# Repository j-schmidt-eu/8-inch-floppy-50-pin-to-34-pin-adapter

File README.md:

# 8-inch floppy drive - 50-pin to 34-pin adapter Rev. 2

> The 50-pin to 34-pin adapter can be used to adapt 8-inch floppy disk drives (using a 50-pin connector) to be controlled by 3.5-inch and 5.25-inch floppy controllers (using a 34-pin connector).

## Table of Contents
- [Introduction](#Introduction)
- [Specifications](#Specifications)
- [Setup](#Setup)
- [Operation](#Operation)
- [Compatibility](#Compatibility)
- [Manufacturing](#Manufacturing)
- [Firmware](#Firmware)
- [FAQ](#FAQ)
- [Licensing](#Licensing)

## Introduction
Many 8-inch floppy drives use a 50-pin card-edge connector to link them to a controller. This is a problem, since modern floppy controllers use a 34-pin IDC connector.
To solve this problem an adapter is necessary that connects compatible signals and generates signals that are unique to the 8-inch floppy drives.
This project aims to provide the schematic, PCB design and firmware source code to build such an adapter.
All compatible signals are directly linked from the 50-pin connector to the 34-pin connector.
Other signals are generated with an onboard microcontroller.

## Specifications
- Power
  - Input voltage: 5V DC
  - Maximum input current: 750mA
  - Connector: 4-pin Berg/Amphenol
- Maximum number of drives per adapter: 2
- Maximum number of adapters per controller: 1
- Pass-through signals:

  | Direction | Name |
  | --------- | ---- |
  | IN        | Index |
  | OUT       | Drive select A |
  | OUT       | Drive select B |
  | OUT       | Direction |
  | OUT       | Step |
  | OUT       | Write data |
  | OUT       | Write gate |
  | IN        | Track 0 |
  | IN        | Write protect |
  | IN        | Read data |
  | OUT       | Side select |
- Generated signals:

  | Direction | Name | Signal source |
  | --------- | ---- | ------------- |
  | OUT       | TG43 (Track greater than 43) /<br>Reduce write current /<br>Filter switch | Determined by tracking the head position.<br>Multiple options available (e.g. control via external signal) |
  | OUT       | Head load | Derived from Motor enable signal.<br>Multiple options available (e.g. control via external signal) |
  | IN        | Ready | Derived from ready signal.<br>Can be disabled by removing a solder jumper bridge JP1 |

## Setup
The adapter can drive up to two drives.

### Floppy drive
A single drive should always be jumpered to be drive A.
The drive should have the termination resistors enabled/present.

A two drive setup should have one drive jumpered to be drive A and the other to be drive to be jumpered drive B.
The last drive (the drive connected at the end of the 50-pin ribbon cable) should have the termination resistors enabled/present, the other drive must have the termination resistors disabled/removed.

__**Important: Only one set of termination resistors must be enabled/present! Having more than one termination resistors enabled/present can damage the adapter and the floppy controller!**__

### Connections

#### Data
To connect the controller to the adapter, use a 34-pin ribbon cable (IDC socket connector to IDC socket connector).
It is recommended to connect the adapter after the twist in the ribbon cable. 

_Note: **When using straight cable without twist, drive A and drive B will be swapped on the controller side.**_

The drive(s) should be connected to the adapter with a 50-pin ribbon cable (IDC card edge connector to IDC socket connector).

#### Power
The adapter should be connected to a power supply via the 4 pin Berg/Amphenol connector (only the 5V line will be used). The pinout is ATX compatible.
Power for the floppy drive(s) should be supplied as described in the operations manual for that specific drive.

## Operation
To operate the adapter a single push button (command button) is present on the bottom right corner of the PCB.

_Note: **The button will be disabled when any drive is in use.**_

### Display
For status display and settings, a two-digit seven-segment display is present on the top right corner of the PCB.
A short press on the command button can be used to cycled between the following display modes:

| Mode | Dot status | Description | Range |
| ---- | ---- | ----------- | ----- |
| Track | Left: off<br>Right: on | Current head position | 0 ... 80 |
| Speed | Left: on (positive value) / blink (negative value)<br>Right: off | Percent deviation from nominal rotational speed | -9.9% ... 9.9% |
| Revision | Left: blink<br>Right: blink<br>Alternates between left and right | Software revision number | 1 ... 99 |
| Dark | Left: off<br>Right: off | Disables display | - |

### Settings
To edit the settings of the adapter the setup menu can be entered by pressing the command button for longer than two seconds.
When navigating the setup menu both dots will be lit.
A short press on the command button can be used to cycled between the menu items.
Item value editing can be enabled and disabled by pressing the command button for longer than two seconds.
During editing both dots will blink simultaneously.
A short press on the command button can be used to cycled between value.

To exit the setup menu, navigate to the Exit item and press the command button for longer than two seconds.

The following menu items are available (in listed order):

| Item | Display | Description | Values | Default |
| ---- | ------- | ----------- | ------ | ------- |
| Default display mode | Left: 1<br>Right: value | Default display mode after adapter power up | 0: Track<br>1: Speed<br>2: Revision<br>3: Dark | 0: Track |
| Drive A<br>Maximum track number | Left/Right: value | Maximum track number that the drive can step to | 32 ... 80 | 76 |
| Drive A<br>TGxx signal | Left: 3<br>Right: value | Source for TG43 / reduce write current / filter signal | 0: Use thresholds<br>1: Always active<br>2: Always inactive<br>3: From external signal | 0: Use thresholds |
| Drive A<br>Head load signal | Left: 4<br>Right: value | Source for head load signal | 0: From [motor A enable]<br>1: Always active<br>2: Always inactive<br>3: From external signal | 0: From [motor A enable] |
| Drive A<br>TGxx write threshold | Left/Right: value | Track number threshold (greater or equal) for TGxx signal active when writing | 0 ... 99 | 44 |
| Drive A<br>TGxx read threshold | Left/Right: value | Track number threshold (greater or equal) for TGxx signal active when reading | 0 ... 99 | 99 |
| Drive B<br>Maximum track number | Left/Right: value | Maximum track number that the drive can step to | 32 ... 80 | 76 |
| Drive B<br>TGxx signal | Left: 8<br>Right: value | Source for TG43 / reduce write current / filter signal | 0: Use thresholds<br>1: Always active<br>2: Always inactive<br>3: From external signal | 0: Use thresholds |
| Drive B<br>Head load signal | Left: 9<br>Right: value | Source for head load signal | 0: From [motor B enable]<br>1: Always active<br>2: Always inactive<br>3: From external signal | 0: From [motor B enable] |
| Drive B<br>TGxx write threshold | Left/Right: value | Track number threshold (greater or equal) for TGxx signal active when writing | 0 ... 99 | 44 |
| Drive B<br>TGxx read threshold | Left/Right: value | Track number threshold (greater or equal) for TGxx signal active when reading | 0 ... 99 | 99 |
| Exit | Left/Right: dark | - | - | - |

_Note: **The external signal cannot distinguish between multiple signals, therefore it should only be assigned to a single signal.**_

The settings are permanently stored when exiting the setup menu.

## Compatibility
The following list shows some 8-inch floppy drive models and the respective settings that should be correct for them.

| Model | TGxx signal | TGxx write threshold | TGxx read threshold | Head load signal | Maximum track number<sup>1</sup> | Tested<sup>2</sup> |
| ----- | ----------- | -------------------- | ------------------- | ---------------- | -------------------- | ------ |
| Mitsubishi M2896-63 | 0: Use thresholds <sup>4</sup> | 44 | 99 | 0: From [motor enable]  | 76(?) | ❓ |
| NEC FD1165 | 0: Use thresholds | 44 | 44 | 0: From [motor enable] | 76(?) | ❓ |
| Shugart SA800<br>Shugart SA801 | 0: Use thresholds <sup>3</sup> | 44 | 99 | 0: From [motor enable] <sup>4</sup> | 76(?) | ❓ |
| Shugart SA810<br>Shugart SA860 | 0: Use thresholds <sup>4</sup> | 44 | 99 | 0: From [motor enable] <sup>4</sup> | 76(?) | ❓ |
| Shugart SA850<br>Shugart SA851 | 0: Use thresholds <sup>4</sup> | 44 | 99 | 0: From [motor enable] <sup>4</sup> | 76(?) | ❓ |
| Tandon TM848-1E<br>Tandon TM848-2E | 0: Use thresholds <sup>4</sup> | 44 | 99 | 0: From [motor enable] <sup>4</sup> | 76(?) | ❓ |
| Y-E DATA YD-180 | 0: Use thresholds | 44 | 60 | 0: From [motor enable] <sup>4</sup> | 79 | ✅ |

<sup>1</sup> Actual seekable track number; track numbering starts at zero.<br>
<sup>2</sup> ✅: Settings have been successfully tested. ❓: Settings should be correct according to the manual, but haven't been tested yet.<br>
<sup>3</sup> Switching is done internally.<br>
<sup>4</sup> Switching is done internally by default; external switching is available optionally (see manual).

## Manufacturing
The schematics and PCB were designed using [KiCad](https://kicad-pcb.org/). The KiCad project is located in the [Schematics & PCB](Schematics%20&%20PCB) folder. 

### Schematic
[PDF](Schematics%20&%20PCB/50%20pin%20to%2034%20pin%20Floppy%20Adapter%20v2/50%20pin%20to%2034%20pin%20Floppy%20Adapter.pdf)

[PNG](Schematics%20&%20PCB/50%20pin%20to%2034%20pin%20Floppy%20Adapter%20v2/50%20pin%20to%2034%20pin%20Floppy%20Adapter.png)

### PCB Gerber files
[ZIP](Schematics%20&%20PCB/50%20pin%20to%2034%20pin%20Floppy%20Adapter%20v2/pcb.zip)

### PCB manufacturing
The board has a size of 100mm x 28.5mm, a minimum trace distance of 0.2mm and the minimal drill diameter is 0.4mm.
There are two layers and a total of 166 holes to drill. All holes, except for the two mounting holes, are plated.

If you are within the EU, you may want to consider choosing AISLER as your PCB manufacturer.

[PCB on AISLER](https://aisler.net/p/LBENFXQV)

### Bill of materials
| Reference | Component | Housing /<br>Footprint | Type | Quantity |
| --------- | --------- | ---------------------- | ---- | -------- |
| C1 | Capacitor 100nF 10V | 0402 | Murata GRM155R61A104JA01D<sup>5</sup> | 1 |
| C2 | Tantalum Capacitor 10µF 6.3V  | B / EIA-3528-21 | Kemet T491B106K006AT<sup>5</sup>  | 1 |
| J1 | 34 pin box header | 2 x 17 x 2.54mm | Connfly DS1013-34SSIB1-B-0<sup>5</sup> | 1 |
| J2 | 4 pin Berg connector | 1 x 4 x 2.54mm | econ connect FK03PN<sup>5</sup> | 1 |
| J3 | 50 pin box header | 2 x 25 x 2.54mm | Connfly DS1013-50SSIB1-B-0<sup>5</sup> | 1 |
| ~~J4~~<sup>6</sup> | ~~3 pin header~~ | ~~1 x 3 x 2.54mm~~ | ~~Connfly DS1021-1*3SF1-1~~<sup>5</sup> | ~~1~~ |
| J5 | 5 pin socket | 1 x 5 x 2.54mm | Connfly DS1023-1*5S21<sup>5</sup> | 1 |
| R2 | Resistor 22kOhm 1/8W 5% | 0805 | Vishay CRCW080522K0FKEA<sup>5</sup> | 1 |
| R1, R3-R4 | Resistor 1kOhm 1/8W 5% | 0805 | Vishay CRCW08051K00FKEA<sup>5</sup> | 3 |
| RN1-RN2, RN5-RN6 | Resistor array 150Ohm 1/16W 5% | 4 x 0603 (1206) convex | Panasonic EXB38V151JV<sup>5</sup> | 4 |
| SW1 | SMD Push button 6mm x 6mm | 9.5mm x 5.8mm | C&K PTS645SK50SMTR92LFS<sup>5</sup> | 1 |
| U1 | PIC18 MCU | QFN-28, 6mm x 6mm, pitch 0.65mm | Microchip PIC18F26K22-I/ML | 1 |
| U2-U3 | BCD to 7-segment decoder | SOP-16, 4.55mm x 10.3mm, pitch 1.27mm | NXP HEF4543B | 2 |
| U4 | Dual buffer | SOT-363 / SC-70-6 | ON Semi NC7WZ16P6X | 1 |
| U5-U6 | Seven segment display | 7mm x 15mm | Kingbright KCSA03-101 | 2 |
| U8 | Dual three-state buffer | VSSOP-8, 2.3mm x 2mm, pitch 0.5mm | ON Semi NC7WZ125K8X | 1 |

<sup>5</sup> Suggestion; Other types may be used. <br>
<sup>6</sup> Not populated; Pin header may be placed, when needed.

### PCB component placement
When soldering the components to the PCB, it is recommended to place them in the following order:
1. Bottom side, hot air: RN1-RN2, RN5-RN6, R2, U2, U3, U8
2. Top side, hot air: C1, C2, R1, R3, R4, U4, U1
3. Top side, soldering iron: U5, U6, SW1, J1, J3, J5, J2
4. Do not populate: J4 (place pin header when needed)

## Firmware
The software for the microcontroller was designed in [MPLAB X IDE](https://www.microchip.com/mplab/mplab-x-ide).
It is written in C and compiled with the [MPLAB XC8 compiler](https://www.microchip.com/mplab/compilers).
A programming adapter is required to transfer the firmware into the microcontroller. The programming socket J5 is designed to match the pinout of the [MPLAB PICkit 4](https://www.microchip.com/developmenttools/ProductDetails/PG164140) (and older) programmers.
The MPLAB X IDE project is located in the [Firmware](Firmware) folder. 

## FAQ
##### My drive is not listed in the compatibility list, will it work?
>**Check the manual of your drive to see if it needs any additional signals like TG43 and Head load.
If so, check if one of the available options matches the behavior required by the drive. When that is the case, the drive will very likely work.**

## Licensing
This project is licensed under the [CC BY-NC-ND 4.0 license](LICENSE).

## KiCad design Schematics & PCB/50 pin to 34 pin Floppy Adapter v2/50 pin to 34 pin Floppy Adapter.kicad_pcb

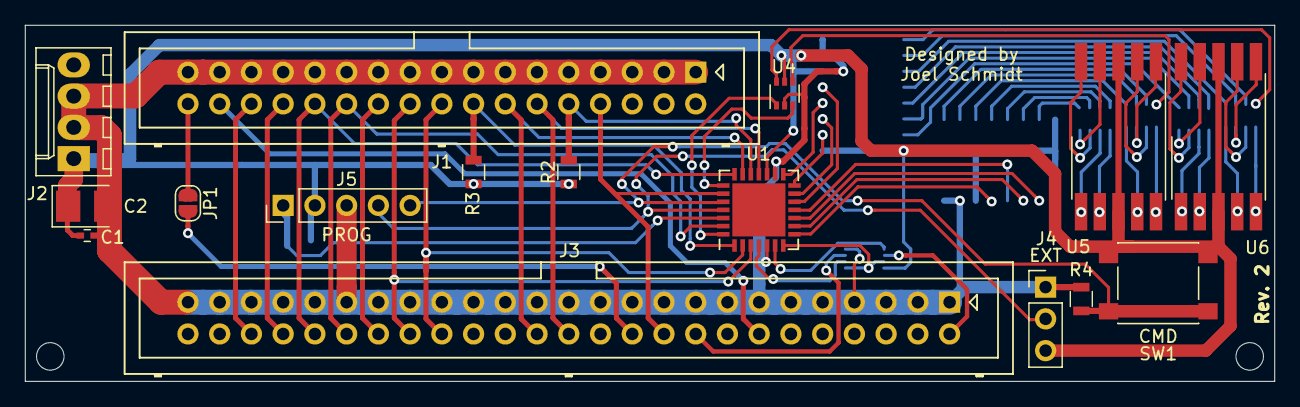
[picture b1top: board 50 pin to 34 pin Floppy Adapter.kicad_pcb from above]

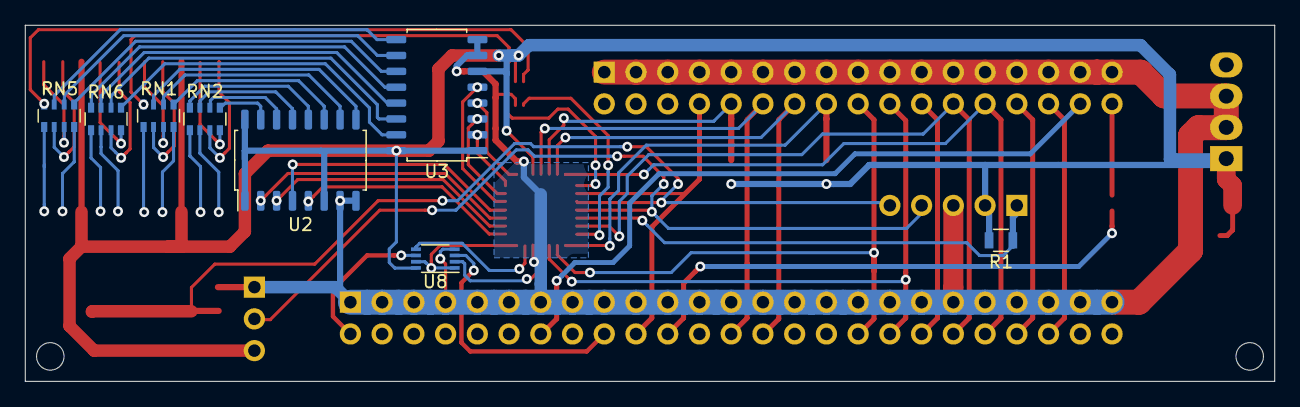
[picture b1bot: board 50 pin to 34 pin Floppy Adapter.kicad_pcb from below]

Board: 2 copper layers, 100.0 x 28.5 mm, 24 parts (8 on the bottom side), 67 nets.

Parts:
C1: 100n; C_0402
C2: 10u; CP_Tantalum_Case-B_EIA-3528-21_Reflow
J1: PC34; Multicomp_MC9A12-3434_2x17x2.54mm_Straight
J2: PWR; TE_171825-4x2.50mm_Straight
J3: FDD50; Multicomp_MC9A12-5034_2x25x2.54mm_Straight
J4: EXT; Pin_Header_Straight_1x03_Pitch2.54mm
J5: PROG; Pin_Header_Straight_1x05_Pitch2.54mm
JP1: Jumper_2_Bridged; SolderJumper-2_P1.3mm_Open_RoundedPad1.0x1.5mm
R1: 22K; R_0805
R2, R3, R4: 1K; R_0805
RN1, RN2, RN5, RN6: 150R; R_Array_Convex_4x0603
SW1: CMD; SW_SPST_PTS645
U1: PIC18F26K22-I/ML; QFN-28-1EP_6x6mm_Pitch0.65mm
U2, U3: HEF4543B; SOP-16_4.55x10.3mm_P1.27mm
U4: NC7WZ16P6X; SOT-363_SC-70-6
U5, U6: KCSA03-101
U8: NC7WZ125K8X; VSSOP-8_2.3x2mm_Pitch0.5mm

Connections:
5V0: C1.1, C2.1, J2.1, J4.3, J5.2, R1.2, R2.1, R3.1, SW1.2, U1.17, U2.1, U2.6, U2.16, U3.1, U3.6, U3.16, U4.5, U5.3, U5.8, U6.3, U6.8, U8.8
/1A: RN1.6, U5.7
/1B: RN1.7, U5.6
/1C: RN1.8, U5.4
/1D: RN2.5, U5.2
/1D0: U1.8, U2.5
/1D1: U1.9, U2.3
/1D2: U1.10, U2.2
/1D3: U1.11, U2.4
/1DP: RN1.4, U4.4
/1E: RN2.6, U5.1
/1F: RN2.8, U5.9
/1G: RN2.7, U5.10
/1H: RN1.5, U5.5
/2A: RN5.6, U6.7
/2B: RN5.7, U6.6
/2C: RN5.8, U6.4
/2D: RN6.5, U6.2
/2D0: U1.12, U3.5
/2D1: U1.13, U3.3
/2D2: U1.14, U3.2
/2D3: U1.15, U3.4
/2DP: RN5.4, U4.6
/2E: RN6.6, U6.1
/2F: RN6.8, U6.9
/2G: RN6.7, U6.10
/2H: RN5.5, U6.5
/PGC: J5.5, R4.1, SW1.1, U1.24
/PGD: J4.2, J5.4, U1.25
/~DIRECTION: J1.18, J3.34, U1.2
/~DISK_CHANGE/READY: J1.34, JP1.1
/~DRIVE_SELECT_0: J1.12, J3.26, U1.18
/~DRIVE_SELECT_1: J1.14, J3.28, U1.20
/~HEAD_LOAD: J3.18, U8.3
/~INDEX: J1.8, J3.20, U1.23
/~MCLR: J5.1, R1.1, U1.26
/~MOTOR_ENABLE_A: J1.10, R2.2, U1.19
/~MOTOR_ENABLE_B: J1.16, R3.2, U1.1
/~READY: J3.22, JP1.2
/~READ_DATA: J1.30, J3.46
/~SIDE_SELECT: J1.32, J3.14
/~STEP: J1.20, J3.36, U1.3
/~TG43/WRITE_CURRENT: J3.2, U8.6
/~TRACK_00: J1.26, J3.42, U1.21
/~WRITE_DATA: J1.22, J3.38
/~WRITE_GATE: J1.24, J3.40, U1.27
/~WRITE_PROTECT: J1.28, J3.44
GND: C1.2, C2.2, J1.1, J1.3, J1.5, J1.7, J1.9, J1.11, J1.13, J1.15, J1.17, J1.19, J1.21, J1.23, J1.25, J1.27, J1.29, J1.31, J1.33, J2.2, J2.3, J3.1, J3.3, J3.5, J3.7, J3.9, J3.11, J3.13, J3.15, J3.17, J3.19, J3.21, J3.23, J3.25, J3.27, J3.29, J3.31, J3.33, J3.35, J3.37, J3.39, J3.41, J3.43, J3.45, J3.47, J3.49, J4.1, J5.3, R4.2, U1.5, U1.16, U2.7, U2.8, U3.7, U3.8, U4.2, U8.4
unnamed: RN1.1, U2.11
unnamed: RN1.2, U2.10
unnamed: RN1.3, U2.9
unnamed: RN2.1, U2.15
unnamed: RN2.2, U2.14
unnamed: RN2.3, U2.13
unnamed: RN2.4, U2.12
unnamed: RN5.1, U3.11
unnamed: RN5.2, U3.10
unnamed: RN5.3, U3.9
unnamed: RN6.1, U3.15
unnamed: RN6.2, U3.14
unnamed: RN6.3, U3.13
unnamed: RN6.4, U3.12
unnamed: U1.4, U8.2
unnamed: U1.6, U8.5
unnamed: U1.7, U8.1, U8.7
unnamed: U1.22, U4.3
unnamed: U1.28, U4.1

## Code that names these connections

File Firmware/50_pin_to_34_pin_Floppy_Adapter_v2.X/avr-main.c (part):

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#define DEBOUNCE_TIME 25
#define LONG_PRESS_TIME 2000

#define MOTOR_ENABLE_A PORTBbits.RB1
#define MOTOR_ENABLE_B PORTAbits.RA2
#define DIRECTION PORTAbits.RA3
#define STEP PORTAbits.RA4
#define HEAD_LOAD PORTAbits.RA7
#define TG43_WRITE_CURRENT PORTAbits.RA5
#define DEVICE_SELECT_0 PORTBbits.RB0
#define DEVICE_SELECT_1 PORTBbits.RB2
#define TRACK_0 PORTBbits.RB3
#define WRITE_GATE PORTAbits.RA0
#define INDEX PORTBbits.RB5
#define CMD_SWITCH PORTBbits.RB6
#define EXT_SIGNAL PORTBbits.RB7

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        {
            OUTPUT_ENABLE = 0;
            
            HEAD_LOAD = 1;
            TG43_WRITE_CURRENT = 1;
            
            // Command button
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
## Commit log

2024-02-12 PCB, firmware and readme for revision 1.
2024-02-12 PCB, firmware and readme for revision 2.
